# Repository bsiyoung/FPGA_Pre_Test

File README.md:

# FPGA_Pre_Test

This simple project is for testing power rails and external oscillator to use them on FPGA circuit design.

## 1. Objectives
1. Check power rails ON/OFF sequencing works properly
2. Check oscillator(25MHz) works properly
3. Get output voltage ripple data by
    + different output capacitance(~200uF) of buck converter
    + different output voltages(1.0~5.0V) of buck converter
    + different load(resistive, ~1.5W consume)

## 2. Directores
|Directory|Description|
|---|---|
|calculation|files for calculation|
|datasheet|datasheets of components|
|diagrams|diagrams images|
|eda_model|EDA model files for KiCAD|
|kicad_proj|KiCAD project directory|
|pcb|PCB images and gerber file|
|readme_img|image for readme file|
|schematic|schematic jpg and pdf file|

## 3. Architecture Diagram
### 3.1 Module Diagram

### 3.2 Block Diagram

### 3.3 Ports Diagram

## 4. Circuit Schematic
Footprints of resistors R16~20 will be used as solder jumper.

</br>
Date of basis for price calculation : 2025.10.21. </br>
Refer to <a href="./component_list.xlsx">component_list.xlsx</a> for details. </br>
* Exclude PCB(USD$20.84/5pcs) and resistive load(USD$8.40).

</br>
<b>Total: USD$27.203/pcs</b> (incldue PCB and resistive load)

## 5. PCB Design
Manufacturer : JLC PCB </br>
Gerber File : ./pcb/pcb_gerber.zip (zip file of ./kicad_proj/output)

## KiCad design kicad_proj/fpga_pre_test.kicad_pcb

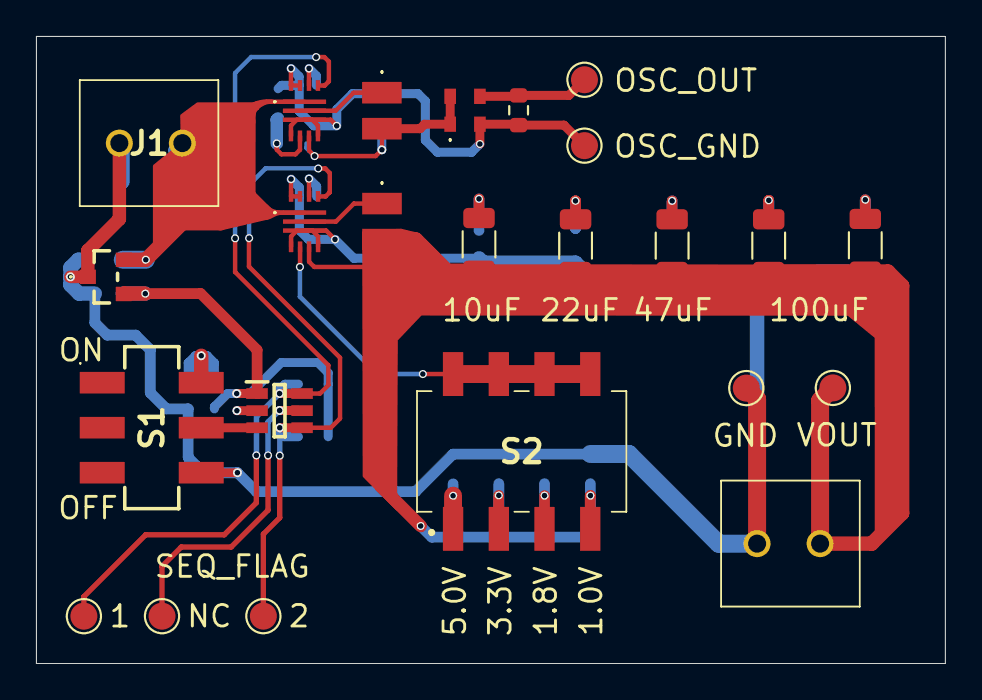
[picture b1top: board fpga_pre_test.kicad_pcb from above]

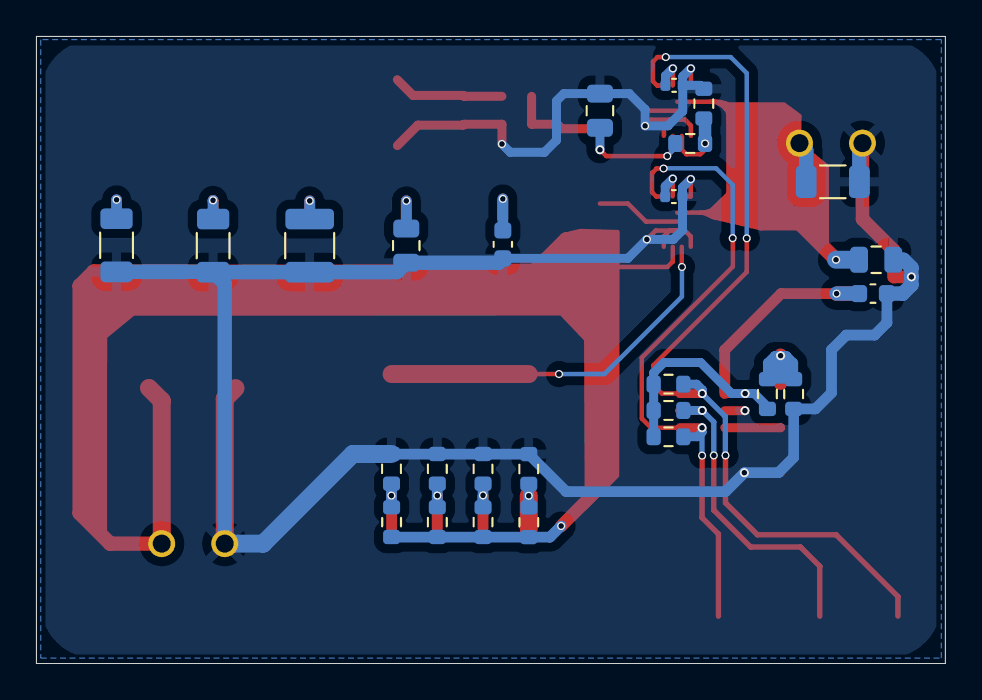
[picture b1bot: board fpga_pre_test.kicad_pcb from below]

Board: 2 copper layers, 50.5 x 34.8 mm, 50 parts (26 on the bottom side), 26 nets.

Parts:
C1: 22uF; C_1206_3216Metric
C2: 4.7uF; C_0805_2012Metric
C3: 4.7uF; C_0603_1608Metric
C4, C6: 22nF; C_0402_1005Metric
C5, C8: 22uF; C_0805_2012Metric
C7: 10uF; C_0603_1608Metric
C9: 47uF; C_1210_3225Metric
C10, C11: 100uF; C_1206_3216Metric
IC1: ZMR330FTA
IC2: LM3880MFX-1AB_NOPB; SOT95P280X145-6N
IC3, IC4: TPS62147RGXT
J1, J2: T50201500000G
L1, L2: 74479325207222
R1: 33k; R_0603_1608Metric
R2, R3, R4, R5, R8: 100k; R_0603_1608Metric
R6, R10, R12: 205k; R_0603_1608Metric
R7, R11: 130k; R_0603_1608Metric
R9: 226k; R_0603_1608Metric
R13: 54.9k; R_0603_1608Metric
R14: 634k; R_0603_1608Metric
R15: 102k; R_0603_1608Metric
R16, R17, R18, R19, R20: 0; R_1206_3216Metric
R21: 14.7k; R_0603_1608Metric
S1: JS202011SCQN
S2: 219-4MST; 2194MST
TP_LOAD_GND1: TestPoint; TestPoint_Pad_D1.5mm
TP_LOAD_VCC1: TestPoint; TestPoint_Pad_D1.5mm
TP_OSC_GND1: TestPoint; TestPoint_Pad_D1.5mm
TP_OSC_OUT1: TestPoint; TestPoint_Pad_D1.5mm
TP_SEQ_FLAG1, TP_SEQ_FLAG2: TestPoint; TestPoint_Pad_D1.5mm
TP_SEQ_FLAG_NC1: TestPoint; TestPoint_Pad_D1.5mm
Y1: ASDMB-25.000MHZ-XY-T; AbraconASDMB

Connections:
/3V3LVR: C3.1, IC1.2 (OUT), IC2.1 (VCC), R1.1, R3.1, R4.1, R5.1
/SEQ_EN: IC2.3 (EN), S1.5
/SEQ_FLAG1: IC2.6 (FLAG1), IC3.8 (EN), R3.2, TP_SEQ_FLAG1.1
/SEQ_FLAG2: IC2.4 (FLAG3), IC4.8 (EN), R5.2, TP_SEQ_FLAG2.1
/SEQ_FLAG_NC: IC2.5 (FLAG2), R4.2, TP_SEQ_FLAG_NC1.1
/VDC: C1.1, C2.1, IC1.3 (IN), IC3.1 (VIN), IC4.1 (VIN), J1.2
/VOUT1: C5.1, IC3.6 (VOS), L1.2, R6.1, Y1.1 (STANDBY), Y1.4 (VDD)
/VOUT2: IC4.6 (VOS), J2.1, L2.2, R8.1, R10.1, R12.1, R14.1, R16.1, R17.1, R18.1, R19.1, R20.1, TP_LOAD_VCC1.1
GND: C1.2, C2.2, C3.2, C4.2, C5.2, C6.2, C7.2, C8.2, C9.2, C10.2, C11.2, IC1.1 (GND), IC2.2 (GND), IC3.3 (GND), IC3.4 (AGND), IC3.7 (PG), IC3.10 (MODE), IC3.11 (FSEL), IC4.3 (GND), IC4.4 (AGND), IC4.7 (PG), IC4.10 (MODE), IC4.11 (FSEL), J1.1, J2.2, R2.2, R7.2, R9.2, R11.2, R13.2, R15.2, R21.2, S1.6, TP_LOAD_GND1.1, TP_OSC_GND1.1, Y1.2 (GND)
unnamed: C7.1, R16.2
unnamed: C8.1, R17.2
unnamed: C9.1, R18.2
unnamed: C10.1, R19.2
unnamed: C11.1, R20.2
unnamed: IC3.5 (FB), R6.2, R7.1
unnamed: C4.1, IC3.9 (SS/TR)
unnamed: IC3.2 (SW), L1.1
unnamed: IC4.5 (FB), S2.5, S2.6, S2.7, S2.8
unnamed: C6.1, IC4.9 (SS/TR)
unnamed: IC4.2 (SW), L2.1
unnamed: R1.2, R2.1, S1.4
unnamed: R8.2, R9.1, S2.4
unnamed: R10.2, R11.1, S2.3
unnamed: R12.2, R13.1, S2.2
unnamed: R14.2, R15.1, S2.1
unnamed: R21.1, TP_OSC_OUT1.1, Y1.3 (OUTPUT)

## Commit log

2025-10-04 Add diagrams
2025-10-08 Add Kicad Project, Circuit Schematic Completed
2025-10-08 README.md Hotfix
2025-10-14 Small fixes on circuit schematic
2025-10-14 PCB Design
2025-10-20 PCB Gerber File Added, Component List xlsx Added
2025-10-20 RREADME Hotfix
2025-10-20 README edit
2025-11-02 Update PCB design and cost information
